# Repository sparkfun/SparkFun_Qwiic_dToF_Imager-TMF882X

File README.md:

SparkFun Qwiic dTof Imager TMF882X
========================================

<table class="table table-hover table-striped table-bordered">
  <tr align="center">
   <td><a href="https://www.sparkfun.com/products/19036">TMF8820"></a></td>
   <td><a href="https://www.sparkfun.com/products/19036">TMF8820"></a></td>
   <td><a href="https://www.sparkfun.com/products/19037">TMF8821"></a></td>
   <td><a href="https://www.sparkfun.com/products/19037">TMF8821"></a></td>
  </tr>
  <tr align="center">
   <td><i>Qwiic dToF Imager TMF8820 <br />[ <a href="https://www.sparkfun.com/products/19036">SEN-19036</a> ]</i></td>
   <td><i>Qwiic Mini dToF Imager TMF8820 <br />[ <a href="https://www.sparkfun.com/products/19218">SEN-19218</a> ]</i></td>
   <td><i>Qwiic dToF Imager TMF8821 <br />[ <a href="https://www.sparkfun.com/products/19037">SEN-19037</a> ]</i></td>
   <td><i>Qwiic Mini dToF Imager TMF8821 <br />[ <a href="https://www.sparkfun.com/products/19451">SEN-19451</a> ]</i></td>
  </tr>
</table>

<Basic description of the part.>

Repository Contents
-------------------

* **/Documentation** - Data sheets, additional product information
* **/Hardware** - Eagle design files (.brd, .sch)
* **/Production** - Production panel files (.brd)

Documentation
--------------
  
* **[Installing an Arduino Library Guide](https://learn.sparkfun.com/tutorials/installing-an-arduino-library)** - Basic information on how to install an Arduino library.
* **[Library](https://github.com/sparkfun/SparkFun_TMF882X_dToF_Arduino_Library)** - Arduino library for the Qwiic dToF TMF8820 and TMF8821.
* **[Hookup Guide](https://learn.sparkfun.com/tutorials/2289)** - Basic hookup guide for the dToF TMF8820 and TMF8821 Sensors.

Product Versions
----------------
* [SEN-19036](https://www.sparkfun.com/products/19036) - Qwiic dToF Imager TMF8820
* [SEN-19218](https://www.sparkfun.com/products/19218) - Qwiic Mini dToF Imager TMF8820
* [SEN-19037](https://www.sparkfun.com/products/19037) - Qwiic dToF Imager TMF8821
* [SEN-19451](https://www.sparkfun.com/products/19451) - Qwiic Mini dToF Imager TMF8821

Version History
---------------
* v1.0 - Initial release

License Information
-------------------

This product is _**open source**_! 

Please review the LICENSE.md file for license information. 

If you have any questions or concerns on licensing, please contact technical support on our [SparkFun forums](https://forum.sparkfun.com/viewforum.php?f=152).

Distributed as-is; no warranty is given.

- Your friends at SparkFun.

_<COLLABORATION CREDIT>_

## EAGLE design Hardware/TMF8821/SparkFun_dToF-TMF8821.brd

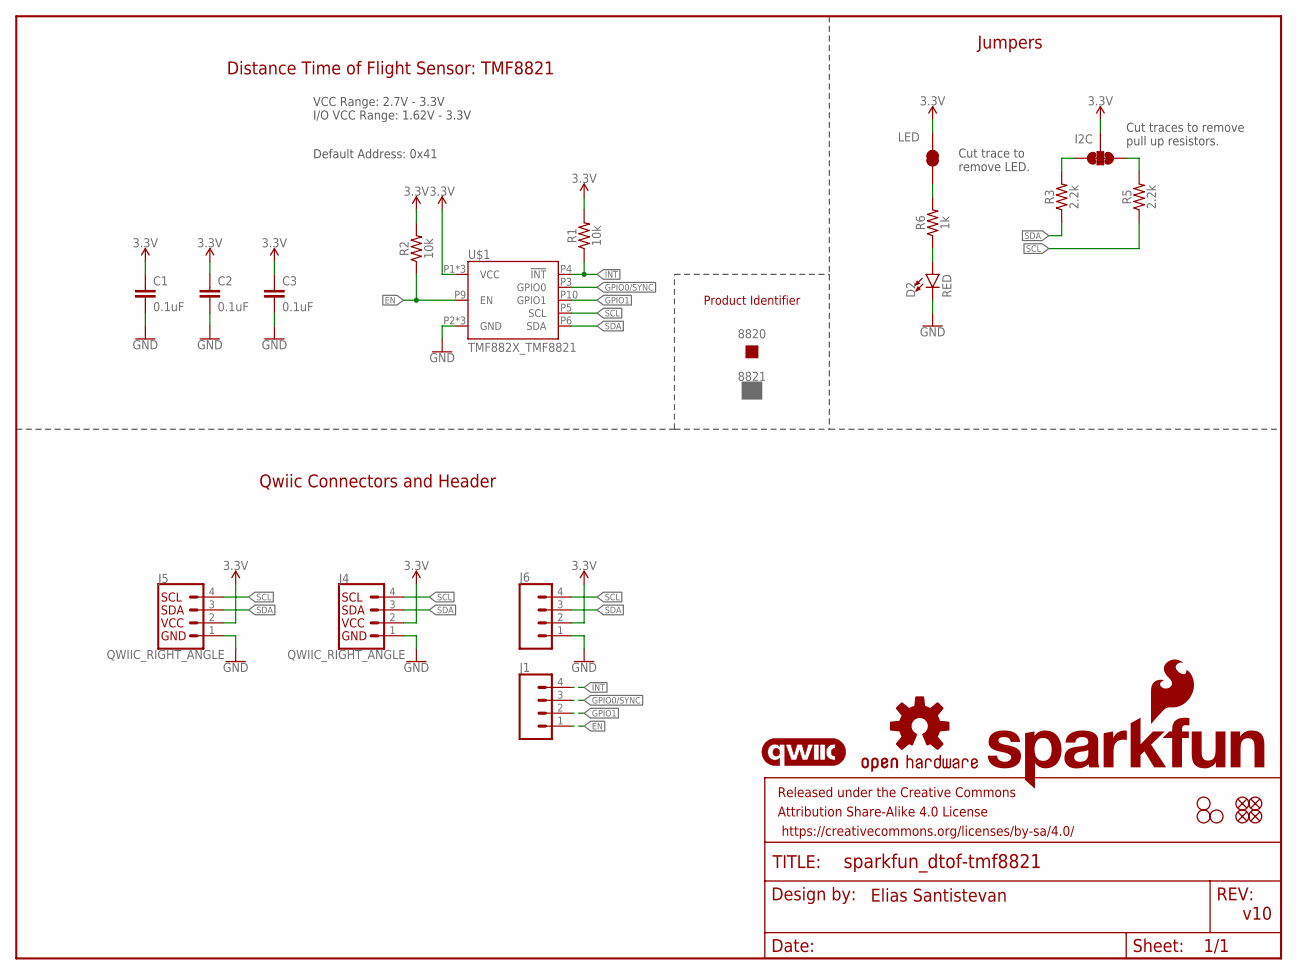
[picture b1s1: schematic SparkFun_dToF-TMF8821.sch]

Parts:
8820: PROD_ID_NO-PASTE_SILK; PRODUCT_IDENT_NO_SILK
8821: PROD_ID_PASTE_SILK; PRODUCT_IDENT_PASTE_SILK
C1, C2, C3: 0.1uF; 0402-TIGHT
D2: RED; LED-0603
FD5, FD6, FD7, FD8: FIDUCIALUFIDUCIAL; FIDUCIAL-MICRO
FRAME2: FRAME-LETTER; CREATIVE_COMMONS
H5, H6, H8: STAND-OFFTIGHT; STAND-OFF-TIGHT
I2C: I2C_PU; SMT-JUMPER_3_2-NC_TRACE_SILK
J1: CONN_041X04_NO_SILK_NO_POP; 1X04_NO_SILK
J4, J5: QWIIC_RIGHT_ANGLE; JST04_1MM_RA
J6: CONN_041X04_NO_SILK; 1X04_NO_SILK
LED: LED; SMT-JUMPER_2_NC_TRACE_SILK
LOGO3: SFE_LOGO_NAME_FLAME.1_INCH; SFE_LOGO_NAME_FLAME_.1
LOGO4: OSHW-LOGOS; OSHW-LOGO-S
R1, R2: 10k; 0603
R3, R5: 2.2k; 0603
R6: 1k; 0603
U$1: TMF882X_TMF8821; TMF882X
U$6: QWIIC_LOGO_5MM; QWIIC_5MM

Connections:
3.3V: C1.1, C2.1, C3.1, I2C.2, J4.2, J5.2, J6.2, LED.2, R1.2, R2.2, U$1.P1 (VCC), U$1.P7 (VCC), U$1.P12 (VCC)
!INT!: J1.4, R1.1, U$1.P4 (!INT!)
EN: J1.1, R2.1, U$1.P9 (EN)
GND: C1.2, C2.2, C3.2, D2.C, J4.1, J5.1, J6.1, U$1.P2 (GND), U$1.P8 (GND), U$1.P11 (GND)
GPIO0/SYNC: J1.3, U$1.P3 (GPIO0)
GPIO1: J1.2, U$1.P10 (GPIO1)
unnamed: D2.A, R6.1
unnamed: LED.1, R6.2
unnamed: I2C.3, R3.2
unnamed: I2C.1, R5.2
SCL: J4.4, J5.4, J6.4, R5.1, U$1.P5 (SCL)
SDA: J4.3, J5.3, J6.3, R3.1, U$1.P6 (SDA)

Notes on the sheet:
v10
Qwiic Connectors and Header
Jumpers
Cut trace to remove LED.
Cut traces to remove pull up resistors.
Elias Santistevan
Distance Time of Flight Sensor: TMF8821
VCC Range: 2.7V - 3.3V I/O VCC Range: 1.62V - 3.3V
Default Address: 0x41
Product Identifier

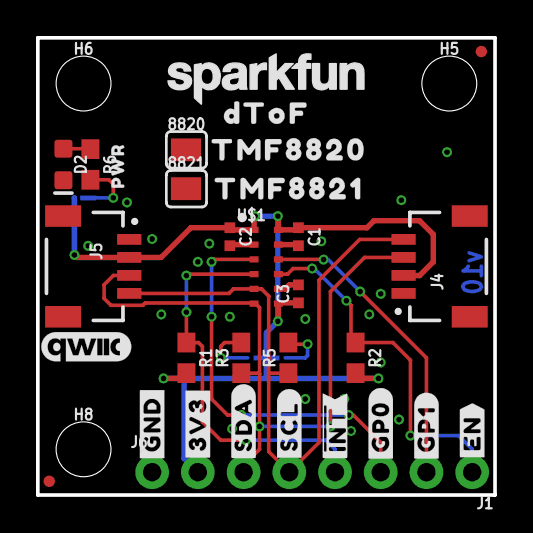
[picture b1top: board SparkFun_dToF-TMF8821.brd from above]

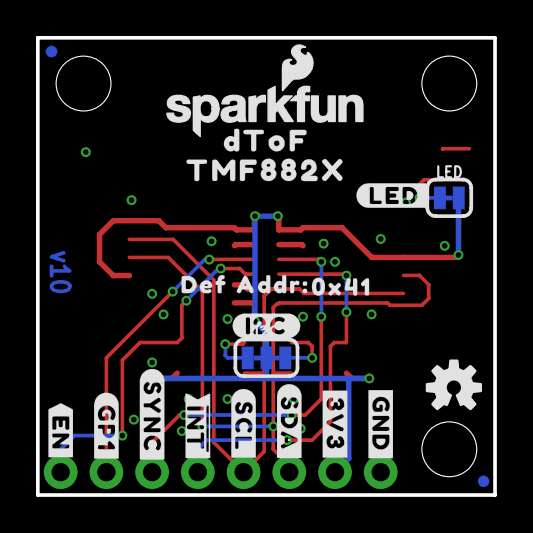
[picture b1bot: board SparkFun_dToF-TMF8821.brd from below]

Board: 2 copper layers, 25.4 x 25.4 mm, 57 parts (21 on the bottom side), 12 nets.

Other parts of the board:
U$2, U$16: #3V3#0
U$3, U$18: #GND#4
U$4, U$23: #SDA#6
U$5, U$21: #SCL#5
U$7, U$17: #EN#7
U$8: #GP0#19
U$9, U$19: #GP1#8
U$10: ##INT##9
U$11, U$26: DTOF882188211
U$12: TMF88209
U$13: SFE_LOGO_NAME_.1
U$14: PWR882188212
U$15: #SYNC#8
U$20: #I2C#11
U$22: #LED#10
U$24: ##INT##8
U$25: TMF882188210
U$27: TMF882X882188211
U$28: DEF11
U$29: ADDR#12
U$30: 0X4113

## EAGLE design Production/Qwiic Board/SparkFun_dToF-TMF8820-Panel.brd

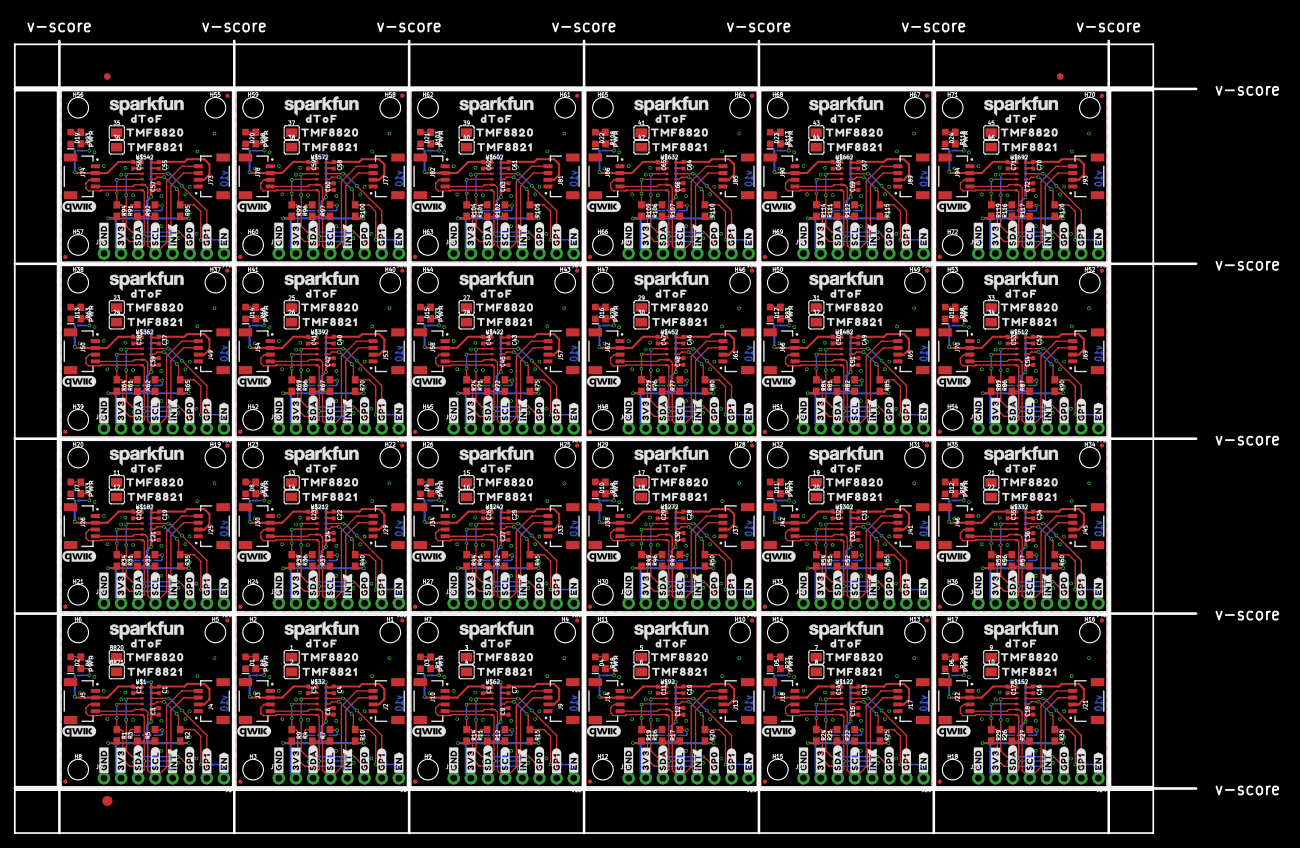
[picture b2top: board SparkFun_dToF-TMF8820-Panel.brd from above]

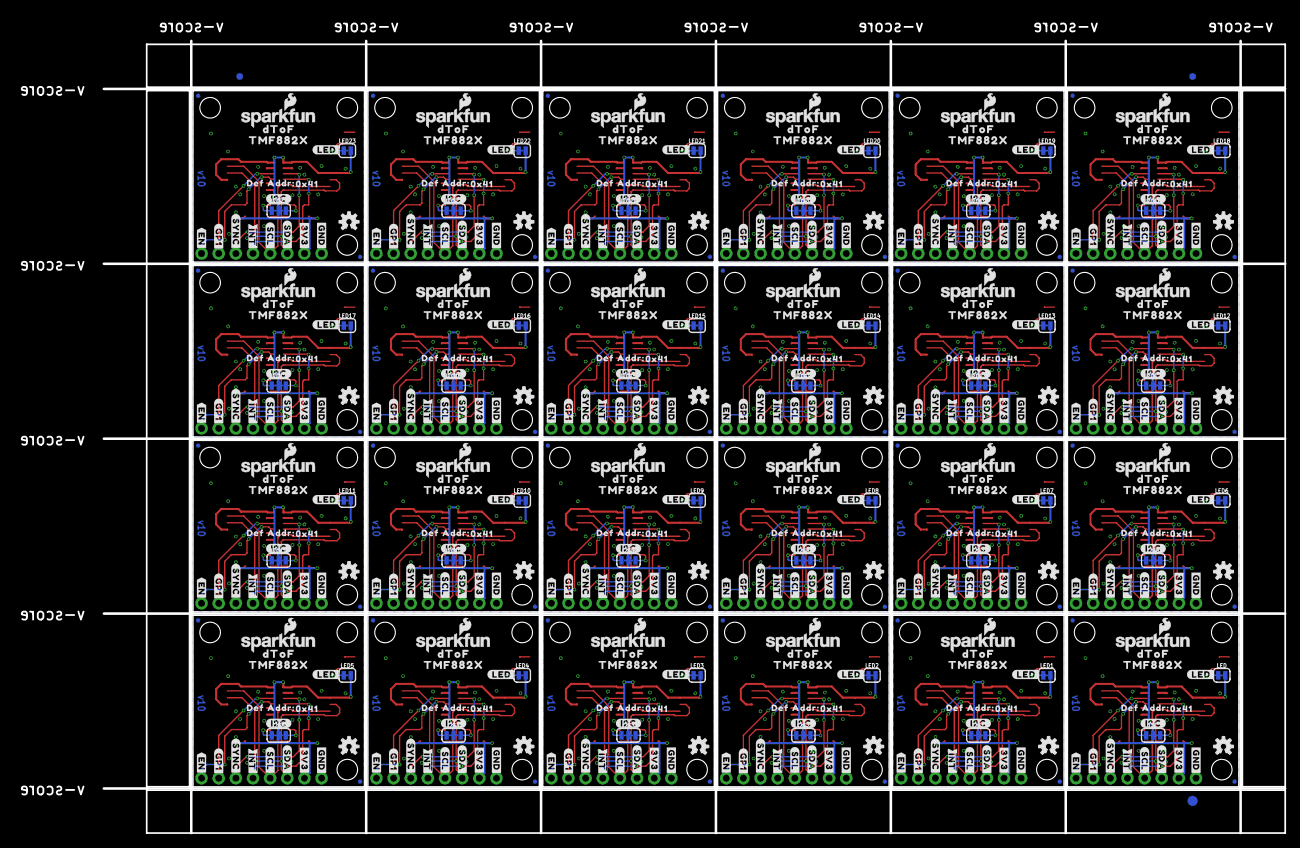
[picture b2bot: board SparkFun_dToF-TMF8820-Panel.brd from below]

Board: 2 copper layers, 175.0 x 117.3 mm, 1350 parts (507 on the bottom side), 288 nets.

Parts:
1, 3, 5, 7, 9, 11, 13, 15, 17, 19, 21, 23, 25, 27, 29, 31, 33, 35, 37, 39, 41, 43, 45, 8820: PROD_ID_PASTE_SILK; PRODUCT_IDENT_PASTE_SILK
2, 4, 6, 8, 10, 12, 14, 16, 18, 20, 22, 24, 26, 28, 30, 32, 34, 36, 38, 40, 42, 44, 46, 8821: PROD_ID_NO-PASTE_SILK; PRODUCT_IDENT_NO_SILK
C1, C2, C3, C4, C5, C6, C7, C8, C9, C10, C11, C12, C13, C14, C15, C16, C17, C18, C19, C20, C21, C22, C23, C24, C25, C26, C27, C28, C29, C30, C31, C32, C33, C34, C35, C36, C37, C38, C39, C40, C41, C42, C43, C44, C45, C46, C47, C48, C49, C50, C51, C52, C53, C54, C55, C56, C57, C58, C59, C60, C61, C62, C63, C64, C65, C66, C67, C68, C69, C70, C71, C72: 0.1uF; 0402-TIGHT
D1, D2, D3, D4, D5, D6, D7, D8, D9, D10, D11, D12, D13, D14, D15, D16, D17, D18, D19, D20, D21, D22, D23, D24: RED; LED-0603
E$1, E$2, E$3, E$4: FIDUCIAL-1X2
E$5, E$6: FIDUCIAL-1.5X3
FD1, FD2, FD3, FD4, FD5, FD6, FD7, FD8, FD9, FD10, FD11, FD12, FD13, FD14, FD15, FD16, FD17, FD18, FD19, FD20, FD21, FD22, FD23, FD24, FD25, FD26, FD27, FD28, FD29, FD30, FD31, FD32, FD33, FD34, FD35, FD36, FD37, FD38, FD39, FD40, FD41, FD42, FD43, FD44, FD45, FD46, FD47, FD48, FD49, FD50, FD51, FD52, FD53, FD54, FD55, FD56, FD57, FD58, FD59, FD60, FD61, FD62, FD63, FD64, FD65, FD66, FD67, FD68, FD69, FD70, FD71, FD72, FD73, FD74, FD75, FD76, FD77, FD78, FD79, FD80, FD81, FD82, FD83, FD84, FD85, FD86, FD87, FD88, FD89, FD90, FD91, FD92, FD93, FD94, FD95, FD96: FIDUCIALUFIDUCIAL; FIDUCIAL-MICRO
H1, H2, H3, H4, H5, H6, H7, H8, H9, H10, H11, H12, H13, H14, H15, H16, H17, H18, H19, H20, H21, H22, H23, H24, H25, H26, H27, H28, H29, H30, H31, H32, H33, H34, H35, H36, H37, H38, H39, H40, H41, H42, H43, H44, H45, H46, H47, H48, H49, H50, H51, H52, H53, H54, H55, H56, H57, H58, H59, H60, H61, H62, H63, H64, H65, H66, H67, H68, H69, H70, H71, H72: STAND-OFFTIGHT; STAND-OFF-TIGHT
I2C, I2C1, I2C2, I2C3, I2C4, I2C5, I2C6, I2C7, I2C8, I2C9, I2C10, I2C11, I2C12, I2C13, I2C14, I2C15, I2C16, I2C17, I2C18, I2C19, I2C20, I2C21, I2C22, I2C23: I2C_PU; SMT-JUMPER_3_2-NC_TRACE_SILK
J1, J6, J7, J8, J11, J12, J15, J16, J19, J20, J23, J24, J27, J28, J31, J32, J35, J36, J39, J40, J43, J44, J47, J48, J51, J52, J55, J56, J59, J60, J63, J64, J67, J68, J71, J72, J75, J76, J79, J80, J83, J84, J87, J88, J91, J92, J95, J96: 1X04_NO_SILK
J2, J3, J4, J5, J9, J10, J13, J14, J17, J18, J21, J22, J25, J26, J29, J30, J33, J34, J37, J38, J41, J42, J45, J46, J49, J50, J53, J54, J57, J58, J61, J62, J65, J66, J69, J70, J73, J74, J77, J78, J81, J82, J85, J86, J89, J90, J93, J94: QWIIC_RIGHT_ANGLE; JST04_1MM_RA
LED, LED1, LED2, LED3, LED4, LED5, LED6, LED7, LED8, LED9, LED10, LED11, LED12, LED13, LED14, LED15, LED16, LED17, LED18, LED19, LED20, LED21, LED22, LED23: LED; SMT-JUMPER_2_NC_TRACE_SILK
LOGO1, LOGO3, LOGO5, LOGO7, LOGO9, LOGO11, LOGO13, LOGO15, LOGO17, LOGO19, LOGO21, LOGO23, LOGO25, LOGO27, LOGO29, LOGO31, LOGO33, LOGO35, LOGO37, LOGO39, LOGO41, LOGO43, LOGO45, LOGO47: SFE_LOGO_NAME_FLAME.1_INCH; SFE_LOGO_NAME_FLAME_.1
LOGO2, LOGO4, LOGO6, LOGO8, LOGO10, LOGO12, LOGO14, LOGO16, LOGO18, LOGO20, LOGO22, LOGO24, LOGO26, LOGO28, LOGO30, LOGO32, LOGO34, LOGO36, LOGO38, LOGO40, LOGO42, LOGO44, LOGO46, LOGO48: OSHW-LOGOS; OSHW-LOGO-S
R1, R2, R9, R10, R14, R15, R19, R20, R24, R25, R29, R30, R34, R35, R39, R40, R44, R45, R49, R50, R54, R55, R59, R60, R64, R65, R69, R70, R74, R75, R79, R80, R84, R85, R89, R90, R94, R95, R99, R100, R104, R105, R109, R110, R114, R115, R119, R120: 10k; 0603
R3, R4, R5, R7, R11, R12, R16, R17, R21, R22, R26, R27, R31, R32, R36, R37, R41, R42, R46, R47, R51, R52, R56, R57, R61, R62, R66, R67, R71, R72, R76, R77, R81, R82, R86, R87, R91, R92, R96, R97, R101, R102, R106, R107, R111, R112, R116, R117: 2.2k; 0603
R6, R8, R13, R18, R23, R28, R33, R38, R43, R48, R53, R58, R63, R68, R73, R78, R83, R88, R93, R98, R103, R108, R113, R118: 1k; 0603
U$1, U$32, U$62, U$92, U$122, U$152, U$182, U$212, U$242, U$272, U$302, U$332, U$362, U$392, U$422, U$452, U$482, U$512, U$542, U$572, U$602, U$632, U$662, U$692: TMF882X_TMF8820; TMF882X
U$2, U$16, U$33, U$39, U$63, U$69, U$93, U$99, U$123, U$129, U$153, U$159, U$183, U$189, U$213, U$219, U$243, U$249, U$273, U$279, U$303, U$309, U$333, U$339, U$363, U$369, U$393, U$399, U$423, U$429, U$453, U$459, U$483, U$489, U$513, U$519, U$543, U$549, U$573, U$579, U$603, U$609, U$633, U$639, U$663, U$669, U$693, U$699: #3V3#0
U$3, U$18, U$34, U$41, U$64, U$71, U$94, U$101, U$124, U$131, U$154, U$161, U$184, U$191, U$214, U$221, U$244, U$251, U$274, U$281, U$304, U$311, U$334, U$341, U$364, U$371, U$394, U$401, U$424, U$431, U$454, U$461, U$484, U$491, U$514, U$521, U$544, U$551, U$574, U$581, U$604, U$611, U$634, U$641, U$664, U$671, U$694, U$701: #GND#4
U$4, U$23, U$35, U$45, U$65, U$75, U$95, U$105, U$125, U$135, U$155, U$165, U$185, U$195, U$215, U$225, U$245, U$255, U$275, U$285, U$305, U$315, U$335, U$345, U$365, U$375, U$395, U$405, U$425, U$435, U$455, U$465, U$485, U$495, U$515, U$525, U$545, U$555, U$575, U$585, U$605, U$615, U$635, U$645, U$665, U$675, U$695, U$705: #SDA#6
U$5, U$21, U$36, U$44, U$66, U$74, U$96, U$104, U$126, U$134, U$156, U$164, U$186, U$194, U$216, U$224, U$246, U$254, U$276, U$284, U$306, U$314, U$336, U$344, U$366, U$374, U$396, U$404, U$426, U$434, U$456, U$464, U$486, U$494, U$516, U$524, U$546, U$554, U$576, U$584, U$606, U$614, U$636, U$644, U$666, U$674, U$696, U$704: #SCL#5
U$6, U$31, U$61, U$91, U$121, U$151, U$181, U$211, U$241, U$271, U$301, U$331, U$361, U$391, U$421, U$451, U$481, U$511, U$541, U$571, U$601, U$631, U$661, U$691: QWIIC_LOGO_5MM; QWIIC_5MM
U$7, U$17, U$37, U$40, U$67, U$70, U$97, U$100, U$127, U$130, U$157, U$160, U$187, U$190, U$217, U$220, U$247, U$250, U$277, U$280, U$307, U$310, U$337, U$340, U$367, U$370, U$397, U$400, U$427, U$430, U$457, U$460, U$487, U$490, U$517, U$520, U$547, U$550, U$577, U$580, U$607, U$610, U$637, U$640, U$667, U$670, U$697, U$700: #EN#7
U$8, U$58, U$88, U$118, U$148, U$178, U$208, U$238, U$268, U$298, U$328, U$358, U$388, U$418, U$448, U$478, U$508, U$538, U$568, U$598, U$628, U$658, U$688, U$718: #GP0#19
U$9, U$19, U$59, U$60, U$89, U$90, U$119, U$120, U$149, U$150, U$179, U$180, U$209, U$210, U$239, U$240, U$269, U$270, U$299, U$300, U$329, U$330, U$359, U$360, U$389, U$390, U$419, U$420, U$449, U$450, U$479, U$480, U$509, U$510, U$539, U$540, U$569, U$570, U$599, U$600, U$629, U$630, U$659, U$660, U$689, U$690, U$719, U$720: #GP1#8
U$10, U$49, U$79, U$109, U$139, U$169, U$199, U$229, U$259, U$289, U$319, U$349, U$379, U$409, U$439, U$469, U$499, U$529, U$559, U$589, U$619, U$649, U$679, U$709: ##INT##9
U$11, U$26, U$50, U$54, U$80, U$84, U$110, U$114, U$140, U$144, U$170, U$174, U$200, U$204, U$230, U$234, U$260, U$264, U$290, U$294, U$320, U$324, U$350, U$354, U$380, U$384, U$410, U$414, U$440, U$444, U$470, U$474, U$500, U$504, U$530, U$534, U$560, U$564, U$590, U$594, U$620, U$624, U$650, U$654, U$680, U$684, U$710, U$714: DTOF882188211
U$12, U$51, U$81, U$111, U$141, U$171, U$201, U$231, U$261, U$291, U$321, U$351, U$381, U$411, U$441, U$471, U$501, U$531, U$561, U$591, U$621, U$651, U$681, U$711: TMF88209
U$13, U$55, U$85, U$115, U$145, U$175, U$205, U$235, U$265, U$295, U$325, U$355, U$385, U$415, U$445, U$475, U$505, U$535, U$565, U$595, U$625, U$655, U$685, U$715: SFE_LOGO_NAME_.1
U$14, U$38, U$68, U$98, U$128, U$158, U$188, U$218, U$248, U$278, U$308, U$338, U$368, U$398, U$428, U$458, U$488, U$518, U$548, U$578, U$608, U$638, U$668, U$698: PWR882188212
U$15, U$52, U$82, U$112, U$142, U$172, U$202, U$232, U$262, U$292, U$322, U$352, U$382, U$412, U$442, U$472, U$502, U$532, U$562, U$592, U$622, U$652, U$682, U$712: #SYNC#8
U$20, U$42, U$72, U$102, U$132, U$162, U$192, U$222, U$252, U$282, U$312, U$342, U$372, U$402, U$432, U$462, U$492, U$522, U$552, U$582, U$612, U$642, U$672, U$702: #I2C#11
U$22, U$43, U$73, U$103, U$133, U$163, U$193, U$223, U$253, U$283, U$313, U$343, U$373, U$403, U$433, U$463, U$493, U$523, U$553, U$583, U$613, U$643, U$673, U$703: #LED#10
U$24, U$53, U$83, U$113, U$143, U$173, U$203, U$233, U$263, U$293, U$323, U$353, U$383, U$413, U$443, U$473, U$503, U$533, U$563, U$593, U$623, U$653, U$683, U$713: ##INT##8
U$25, U$56, U$86, U$116, U$146, U$176, U$206, U$236, U$266, U$296, U$326, U$356, U$386, U$416, U$446, U$476, U$506, U$536, U$566, U$596, U$626, U$656, U$686, U$716: TMF882188210
U$27, U$57, U$87, U$117, U$147, U$177, U$207, U$237, U$267, U$297, U$327, U$357, U$387, U$417, U$447, U$477, U$507, U$537, U$567, U$597, U$627, U$657, U$687, U$717: TMF882X882188211
U$28, U$46, U$76, U$106, U$136, U$166, U$196, U$226, U$256, U$286, U$316, U$346, U$376, U$406, U$436, U$466, U$496, U$526, U$556, U$586, U$616, U$646, U$676, U$706: DEF11
U$29, U$47, U$77, U$107, U$137, U$167, U$197, U$227, U$257, U$287, U$317, U$347, U$377, U$407, U$437, U$467, U$497, U$527, U$557, U$587, U$617, U$647, U$677, U$707: ADDR#12
U$30, U$48, U$78, U$108, U$138, U$168, U$198, U$228, U$258, U$288, U$318, U$348, U$378, U$408, U$438, U$468, U$498, U$528, U$558, U$588, U$618, U$648, U$678, U$708: 0X4113

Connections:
3.3V: C1.1, C2.1, C3.1, I2C.2, J4.2, J5.2, J6.2, LED.2, R1.2, R2.2, U$1.P1, U$1.P7, U$1.P12
3.3V1: C4.1, C5.1, C6.1, I2C1.2, J2.2, J3.2, J7.2, LED1.2, R9.2, R10.2, U$32.P1, U$32.P7, U$32.P12
3.3V2: C7.1, C8.1, C9.1, I2C2.2, J9.2, J10.2, J11.2, LED2.2, R14.2, R15.2, U$62.P1, U$62.P7, U$62.P12
3.3V3: C10.1, C11.1, C12.1, I2C3.2, J13.2, J14.2, J15.2, LED3.2, R19.2, R20.2, U$92.P1, U$92.P7, U$92.P12
3.3V4: C13.1, C14.1, C15.1, I2C4.2, J17.2, J18.2, J19.2, LED4.2, R24.2, R25.2, U$122.P1, U$122.P7, U$122.P12
3.3V5: C16.1, C17.1, C18.1, I2C5.2, J21.2, J22.2, J23.2, LED5.2, R29.2, R30.2, U$152.P1, U$152.P7, U$152.P12
3.3V6: C19.1, C20.1, C21.1, I2C6.2, J25.2, J26.2, J27.2, LED6.2, R34.2, R35.2, U$182.P1, U$182.P7, U$182.P12
3.3V7: C22.1, C23.1, C24.1, I2C7.2, J29.2, J30.2, J31.2, LED7.2, R39.2, R40.2, U$212.P1, U$212.P7, U$212.P12
3.3V8: C25.1, C26.1, C27.1, I2C8.2, J33.2, J34.2, J35.2, LED8.2, R44.2, R45.2, U$242.P1, U$242.P7, U$242.P12
3.3V9: C28.1, C29.1, C30.1, I2C9.2, J37.2, J38.2, J39.2, LED9.2, R49.2, R50.2, U$272.P1, U$272.P7, U$272.P12
3.3V10: C31.1, C32.1, C33.1, I2C10.2, J41.2, J42.2, J43.2, LED10.2, R54.2, R55.2, U$302.P1, U$302.P7, U$302.P12
3.3V11: C34.1, C35.1, C36.1, I2C11.2, J45.2, J46.2, J47.2, LED11.2, R59.2, R60.2, U$332.P1, U$332.P7, U$332.P12
3.3V12: C37.1, C38.1, C39.1, I2C12.2, J49.2, J50.2, J51.2, LED12.2, R64.2, R65.2, U$362.P1, U$362.P7, U$362.P12
3.3V13: C40.1, C41.1, C42.1, I2C13.2, J53.2, J54.2, J55.2, LED13.2, R69.2, R70.2, U$392.P1, U$392.P7, U$392.P12
3.3V14: C43.1, C44.1, C45.1, I2C14.2, J57.2, J58.2, J59.2, LED14.2, R74.2, R75.2, U$422.P1, U$422.P7, U$422.P12
3.3V15: C46.1, C47.1, C48.1, I2C15.2, J61.2, J62.2, J63.2, LED15.2, R79.2, R80.2, U$452.P1, U$452.P7, U$452.P12
3.3V16: C49.1, C50.1, C51.1, I2C16.2, J65.2, J66.2, J67.2, LED16.2, R84.2, R85.2, U$482.P1, U$482.P7, U$482.P12
3.3V17: C52.1, C53.1, C54.1, I2C17.2, J69.2, J70.2, J71.2, LED17.2, R89.2, R90.2, U$512.P1, U$512.P7, U$512.P12
3.3V18: C55.1, C56.1, C57.1, I2C18.2, J73.2, J74.2, J75.2, LED18.2, R94.2, R95.2, U$542.P1, U$542.P7, U$542.P12
3.3V19: C58.1, C59.1, C60.1, I2C19.2, J77.2, J78.2, J79.2, LED19.2, R99.2, R100.2, U$572.P1, U$572.P7, U$572.P12
3.3V20: C61.1, C62.1, C63.1, I2C20.2, J81.2, J82.2, J83.2, LED20.2, R104.2, R105.2, U$602.P1, U$602.P7, U$602.P12
3.3V21: C64.1, C65.1, C66.1, I2C21.2, J85.2, J86.2, J87.2, LED21.2, R109.2, R110.2, U$632.P1, U$632.P7, U$632.P12
3.3V22: C67.1, C68.1, C69.1, I2C22.2, J89.2, J90.2, J91.2, LED22.2, R114.2, R115.2, U$662.P1, U$662.P7, U$662.P12
3.3V23: C70.1, C71.1, C72.1, I2C23.2, J93.2, J94.2, J95.2, LED23.2, R119.2, R120.2, U$692.P1, U$692.P7, U$692.P12
!INT!: J1.4, R1.1, U$1.P4
!INT!1: J8.4, R9.1, U$32.P4
!INT!2: J12.4, R14.1, U$62.P4
!INT!3: J16.4, R19.1, U$92.P4
!INT!4: J20.4, R24.1, U$122.P4
!INT!5: J24.4, R29.1, U$152.P4
!INT!6: J28.4, R34.1, U$182.P4
!INT!7: J32.4, R39.1, U$212.P4
!INT!8: J36.4, R44.1, U$242.P4
!INT!9: J40.4, R49.1, U$272.P4
!INT!10: J44.4, R54.1, U$302.P4
!INT!11: J48.4, R59.1, U$332.P4
!INT!12: J52.4, R64.1, U$362.P4
!INT!13: J56.4, R69.1, U$392.P4
!INT!14: J60.4, R74.1, U$422.P4
!INT!15: J64.4, R79.1, U$452.P4
!INT!16: J68.4, R84.1, U$482.P4
!INT!17: J72.4, R89.1, U$512.P4
!INT!18: J76.4, R94.1, U$542.P4
!INT!19: J80.4, R99.1, U$572.P4
!INT!20: J84.4, R104.1, U$602.P4
!INT!21: J88.4, R109.1, U$632.P4
!INT!22: J92.4, R114.1, U$662.P4
!INT!23: J96.4, R119.1, U$692.P4
EN: J1.1, R2.1, U$1.P9
EN1: J8.1, R10.1, U$32.P9
EN2: J12.1, R15.1, U$62.P9
EN3: J16.1, R20.1, U$92.P9
EN4: J20.1, R25.1, U$122.P9
EN5: J24.1, R30.1, U$152.P9
EN6: J28.1, R35.1, U$182.P9
EN7: J32.1, R40.1, U$212.P9
EN8: J36.1, R45.1, U$242.P9
EN9: J40.1, R50.1, U$272.P9
EN10: J44.1, R55.1, U$302.P9
EN11: J48.1, R60.1, U$332.P9
EN12: J52.1, R65.1, U$362.P9
EN13: J56.1, R70.1, U$392.P9
EN14: J60.1, R75.1, U$422.P9
EN15: J64.1, R80.1, U$452.P9
EN16: J68.1, R85.1, U$482.P9
EN17: J72.1, R90.1, U$512.P9
EN18: J76.1, R95.1, U$542.P9
EN19: J80.1, R100.1, U$572.P9
EN20: J84.1, R105.1, U$602.P9
EN21: J88.1, R110.1, U$632.P9
EN22: J92.1, R115.1, U$662.P9
EN23: J96.1, R120.1, U$692.P9
GND: C1.2, C2.2, C3.2, D2.C, J4.1, J5.1, J6.1, U$1.P2, U$1.P8, U$1.P11
GND1: C4.2, C5.2, C6.2, D1.C, J2.1, J3.1, J7.1, U$32.P2, U$32.P8, U$32.P11
GND2: C7.2, C8.2, C9.2, D3.C, J9.1, J10.1, J11.1, U$62.P2, U$62.P8, U$62.P11
GND3: C10.2, C11.2, C12.2, D4.C, J13.1, J14.1, J15.1, U$92.P2, U$92.P8, U$92.P11
GND4: C13.2, C14.2, C15.2, D5.C, J17.1, J18.1, J19.1, U$122.P2, U$122.P8, U$122.P11
GND5: C16.2, C17.2, C18.2, D6.C, J21.1, J22.1, J23.1, U$152.P2, U$152.P8, U$152.P11
GND6: C19.2, C20.2, C21.2, D7.C, J25.1, J26.1, J27.1, U$182.P2, U$182.P8, U$182.P11
GND7: C22.2, C23.2, C24.2, D8.C, J29.1, J30.1, J31.1, U$212.P2, U$212.P8, U$212.P11
GND8: C25.2, C26.2, C27.2, D9.C, J33.1, J34.1, J35.1, U$242.P2, U$242.P8, U$242.P11
GND9: C28.2, C29.2, C30.2, D10.C, J37.1, J38.1, J39.1, U$272.P2, U$272.P8, U$272.P11
GND10: C31.2, C32.2, C33.2, D11.C, J41.1, J42.1, J43.1, U$302.P2, U$302.P8, U$302.P11
GND11: C34.2, C35.2, C36.2, D12.C, J45.1, J46.1, J47.1, U$332.P2, U$332.P8, U$332.P11
GND12: C37.2, C38.2, C39.2, D13.C, J49.1, J50.1, J51.1, U$362.P2, U$362.P8, U$362.P11
GND13: C40.2, C41.2, C42.2, D14.C, J53.1, J54.1, J55.1, U$392.P2, U$392.P8, U$392.P11
GND14: C43.2, C44.2, C45.2, D15.C, J57.1, J58.1, J59.1, U$422.P2, U$422.P8, U$422.P11
GND15: C46.2, C47.2, C48.2, D16.C, J61.1, J62.1, J63.1, U$452.P2, U$452.P8, U$452.P11
GND16: C49.2, C50.2, C51.2, D17.C, J65.1, J66.1, J67.1, U$482.P2, U$482.P8, U$482.P11
GND17: C52.2, C53.2, C54.2, D18.C, J69.1, J70.1, J71.1, U$512.P2, U$512.P8, U$512.P11
GND18: C55.2, C56.2, C57.2, D19.C, J73.1, J74.1, J75.1, U$542.P2, U$542.P8, U$542.P11
GND19: C58.2, C59.2, C60.2, D20.C, J77.1, J78.1, J79.1, U$572.P2, U$572.P8, U$572.P11
GND20: C61.2, C62.2, C63.2, D21.C, J81.1, J82.1, J83.1, U$602.P2, U$602.P8, U$602.P11
GND21: C64.2, C65.2, C66.2, D22.C, J85.1, J86.1, J87.1, U$632.P2, U$632.P8, U$632.P11
GND22: C67.2, C68.2, C69.2, D23.C, J89.1, J90.1, J91.1, U$662.P2, U$662.P8, U$662.P11
GND23: C70.2, C71.2, C72.2, D24.C, J93.1, J94.1, J95.1, U$692.P2, U$692.P8, U$692.P11
GPIO0/SYNC: J1.3, U$1.P3
GPIO0/SYNC1: J8.3, U$32.P3
GPIO0/SYNC2: J12.3, U$62.P3
GPIO0/SYNC3: J16.3, U$92.P3
GPIO0/SYNC4: J20.3, U$122.P3
GPIO0/SYNC5: J24.3, U$152.P3
GPIO0/SYNC6: J28.3, U$182.P3
GPIO0/SYNC7: J32.3, U$212.P3
GPIO0/SYNC8: J36.3, U$242.P3
GPIO0/SYNC9: J40.3, U$272.P3
GPIO0/SYNC10: J44.3, U$302.P3
GPIO0/SYNC11: J48.3, U$332.P3
GPIO0/SYNC12: J52.3, U$362.P3
GPIO0/SYNC13: J56.3, U$392.P3
GPIO0/SYNC14: J60.3, U$422.P3
GPIO0/SYNC15: J64.3, U$452.P3
GPIO0/SYNC16: J68.3, U$482.P3
GPIO0/SYNC17: J72.3, U$512.P3
GPIO0/SYNC18: J76.3, U$542.P3
GPIO0/SYNC19: J80.3, U$572.P3
GPIO0/SYNC20: J84.3, U$602.P3
GPIO0/SYNC21: J88.3, U$632.P3
GPIO0/SYNC22: J92.3, U$662.P3
GPIO0/SYNC23: J96.3, U$692.P3
GPIO1: J1.2, U$1.P10
GPIO2: J8.2, U$32.P10
GPIO3: J12.2, U$62.P10
GPIO4: J16.2, U$92.P10
GPIO5: J20.2, U$122.P10
GPIO6: J24.2, U$152.P10
GPIO7: J28.2, U$182.P10
GPIO8: J32.2, U$212.P10
GPIO9: J36.2, U$242.P10
GPIO10: J40.2, U$272.P10
GPIO11: J44.2, U$302.P10
GPIO12: J48.2, U$332.P10
GPIO13: J52.2, U$362.P10
GPIO14: J56.2, U$392.P10
GPIO15: J60.2, U$422.P10
GPIO16: J64.2, U$452.P10
GPIO17: J68.2, U$482.P10
GPIO18: J72.2, U$512.P10
GPIO19: J76.2, U$542.P10
GPIO20: J80.2, U$572.P10
GPIO21: J84.2, U$602.P10
GPIO22: J88.2, U$632.P10
GPIO23: J92.2, U$662.P10
GPIO24: J96.2, U$692.P10
unnamed: D1.A, R8.1
unnamed: LED1.1, R8.2
unnamed: I2C1.3, R4.2
unnamed: I2C1.1, R7.2
unnamed: D2.A, R6.1
unnamed: LED.1, R6.2
unnamed: I2C.3, R3.2
unnamed: I2C.1, R5.2
unnamed: D3.A, R13.1
unnamed: LED2.1, R13.2
unnamed: I2C2.3, R11.2
unnamed: I2C2.1, R12.2
unnamed: D4.A, R18.1
unnamed: LED3.1, R18.2
unnamed: I2C3.3, R16.2
unnamed: I2C3.1, R17.2
unnamed: D5.A, R23.1
unnamed: LED4.1, R23.2
unnamed: I2C4.3, R21.2
unnamed: I2C4.1, R22.2
unnamed: D6.A, R28.1
unnamed: LED5.1, R28.2
unnamed: I2C5.3, R26.2
unnamed: I2C5.1, R27.2
unnamed: D7.A, R33.1
unnamed: LED6.1, R33.2
unnamed: I2C6.3, R31.2
unnamed: I2C6.1, R32.2
unnamed: D8.A, R38.1
unnamed: LED7.1, R38.2
unnamed: I2C7.3, R36.2
unnamed: I2C7.1, R37.2
unnamed: D9.A, R43.1
unnamed: LED8.1, R43.2
unnamed: I2C8.3, R41.2
unnamed: I2C8.1, R42.2
unnamed: D10.A, R48.1
unnamed: LED9.1, R48.2
unnamed: I2C9.3, R46.2
unnamed: I2C9.1, R47.2
unnamed: D11.A, R53.1
unnamed: LED10.1, R53.2
unnamed: I2C10.3, R51.2
unnamed: I2C10.1, R52.2
unnamed: D12.A, R58.1
unnamed: LED11.1, R58.2
unnamed: I2C11.3, R56.2
unnamed: I2C11.1, R57.2
unnamed: D13.A, R63.1
unnamed: LED12.1, R63.2
unnamed: I2C12.3, R61.2
unnamed: I2C12.1, R62.2
unnamed: D14.A, R68.1
unnamed: LED13.1, R68.2
unnamed: I2C13.3, R66.2
unnamed: I2C13.1, R67.2
unnamed: D15.A, R73.1
unnamed: LED14.1, R73.2
unnamed: I2C14.3, R71.2
unnamed: I2C14.1, R72.2
unnamed: D16.A, R78.1
unnamed: LED15.1, R78.2
unnamed: I2C15.3, R76.2
unnamed: I2C15.1, R77.2
unnamed: D17.A, R83.1
unnamed: LED16.1, R83.2
unnamed: I2C16.3, R81.2
unnamed: I2C16.1, R82.2
unnamed: D18.A, R88.1
unnamed: LED17.1, R88.2
unnamed: I2C17.3, R86.2
unnamed: I2C17.1, R87.2
unnamed: D19.A, R93.1
unnamed: LED18.1, R93.2
unnamed: I2C18.3, R91.2
unnamed: I2C18.1, R92.2
unnamed: D20.A, R98.1
unnamed: LED19.1, R98.2
unnamed: I2C19.3, R96.2
unnamed: I2C19.1, R97.2
unnamed: D21.A, R103.1
unnamed: LED20.1, R103.2
unnamed: I2C20.3, R101.2
unnamed: I2C20.1, R102.2
unnamed: D22.A, R108.1
unnamed: LED21.1, R108.2
unnamed: I2C21.3, R106.2
unnamed: I2C21.1, R107.2
unnamed: D23.A, R113.1
unnamed: LED22.1, R113.2
unnamed: I2C22.3, R111.2
unnamed: I2C22.1, R112.2
unnamed: D24.A, R118.1
unnamed: LED23.1, R118.2
unnamed: I2C23.3, R116.2
unnamed: I2C23.1, R117.2
SCL: J4.4, J5.4, J6.4, R5.1, U$1.P5
SCL1: J2.4, J3.4, J7.4, R7.1, U$32.P5
SCL2: J9.4, J10.4, J11.4, R12.1, U$62.P5
SCL3: J13.4, J14.4, J15.4, R17.1, U$92.P5
SCL4: J17.4, J18.4, J19.4, R22.1, U$122.P5
SCL5: J21.4, J22.4, J23.4, R27.1, U$152.P5
SCL6: J25.4, J26.4, J27.4, R32.1, U$182.P5
SCL7: J29.4, J30.4, J31.4, R37.1, U$212.P5
SCL8: J33.4, J34.4, J35.4, R42.1, U$242.P5
SCL9: J37.4, J38.4, J39.4, R47.1, U$272.P5
SCL10: J41.4, J42.4, J43.4, R52.1, U$302.P5
SCL11: J45.4, J46.4, J47.4, R57.1, U$332.P5
SCL12: J49.4, J50.4, J51.4, R62.1, U$362.P5
SCL13: J53.4, J54.4, J55.4, R67.1, U$392.P5
SCL14: J57.4, J58.4, J59.4, R72.1, U$422.P5
SCL15: J61.4, J62.4, J63.4, R77.1, U$452.P5
SCL16: J65.4, J66.4, J67.4, R82.1, U$482.P5
SCL17: J69.4, J70.4, J71.4, R87.1, U$512.P5
SCL18: J73.4, J74.4, J75.4, R92.1, U$542.P5
SCL19: J77.4, J78.4, J79.4, R97.1, U$572.P5
SCL20: J81.4, J82.4, J83.4, R102.1, U$602.P5
SCL21: J85.4, J86.4, J87.4, R107.1, U$632.P5
SCL22: J89.4, J90.4, J91.4, R112.1, U$662.P5
SCL23: J93.4, J94.4, J95.4, R117.1, U$692.P5
SDA: J4.3, J5.3, J6.3, R3.1, U$1.P6
SDA1: J2.3, J3.3, J7.3, R4.1, U$32.P6
SDA2: J9.3, J10.3, J11.3, R11.1, U$62.P6
SDA3: J13.3, J14.3, J15.3, R16.1, U$92.P6
SDA4: J17.3, J18.3, J19.3, R21.1, U$122.P6
SDA5: J21.3, J22.3, J23.3, R26.1, U$152.P6
SDA6: J25.3, J26.3, J27.3, R31.1, U$182.P6
SDA7: J29.3, J30.3, J31.3, R36.1, U$212.P6
SDA8: J33.3, J34.3, J35.3, R41.1, U$242.P6
SDA9: J37.3, J38.3, J39.3, R46.1, U$272.P6
SDA10: J41.3, J42.3, J43.3, R51.1, U$302.P6
SDA11: J45.3, J46.3, J47.3, R56.1, U$332.P6
SDA12: J49.3, J50.3, J51.3, R61.1, U$362.P6
SDA13: J53.3, J54.3, J55.3, R66.1, U$392.P6
SDA14: J57.3, J58.3, J59.3, R71.1, U$422.P6
SDA15: J61.3, J62.3, J63.3, R76.1, U$452.P6
SDA16: J65.3, J66.3, J67.3, R81.1, U$482.P6
SDA17: J69.3, J70.3, J71.3, R86.1, U$512.P6
SDA18: J73.3, J74.3, J75.3, R91.1, U$542.P6
SDA19: J77.3, J78.3, J79.3, R96.1, U$572.P6
SDA20: J81.3, J82.3, J83.3, R101.1, U$602.P6
SDA21: J85.3, J86.3, J87.3, R106.1, U$632.P6
SDA22: J89.3, J90.3, J91.3, R111.1, U$662.P6
SDA23: J93.3, J94.3, J95.3, R116.1, U$692.P6

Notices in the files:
parts and their libraries:
SparkFun-Aesthetics: Licensing: Creative Commons ShareAlike 4.0 International - https://creativecommons.org/licenses/by-sa/4.0
SparkFun-Aesthetics: Released under the Creative Commons Attribution Share-Alike 4.0 License
SparkFun-Aesthetics: https://creativecommons.org/licenses/by-sa/4.0
